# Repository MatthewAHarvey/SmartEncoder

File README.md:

# SmartEncoder
Arduino friendly, serially addressable, ATTINY85 based rotary encoders. Reduce the pin count from 3 * n where n is the number of encoders (pins A, B and button C) to 2 total. Serial in, Serial out. Use Hardware Serial, AltSoftSerial or Software Serial

Handling lots of encoders at the same time can be a challenge. For example, in our use case, we had 15 encoders attached to one Arduino Mega. After all the connections to other peripherals, we ran out of pins. The encoders had to be polled since there are not enough interrupts. Our solution is to offload the handling of the encoders to dedicated ATTINY85 chips. These then talk asynchronous serial at 125000 baud in a ring with the master arduino. The arduino now only needs 2 pins: 1 serial tx and 1 serial rx. At the moment this is limited to one of the hardware serial ports but tests show it's possible with software serial implementations.

In order for this to work, the ATTINY85s' clock frequencies must be set more accurately than straight from the factory. 

### Installation instructions:

1. First, the ATTINYs must be frequency calibrated. We do this by burning the arduino bootloader on to an ATTINY and uploading the FreqCal sketch. We use the [ATTINYCore](https://github.com/SpenceKonde/ATTinyCore) which must be installed in the Arduino IDE. We output a square wave from pin 6 and observe it using an oscilloscope. An attached rotary encoder is then used to adjust this signal until it is as close to 1 MHz as possible. Pressing the encoder button saves the current OSCCAL register value to the EEPROM. 

Arduino IDE settings for ATTINY85:

Schematic for the FreqCal rotary encoder programme:

2. Now upload the ATTINY85RotEncCode sketch to each of the ATTINYs.

3. The example SEHandlerTest programme can be uploaded to the master arduino mega.

### To Do:
1. Add individual encoder direction swap command that can be called any time after init().
2. Add global encoder direction swap at creation time that tells all the individual encoders to swap direction at init time.

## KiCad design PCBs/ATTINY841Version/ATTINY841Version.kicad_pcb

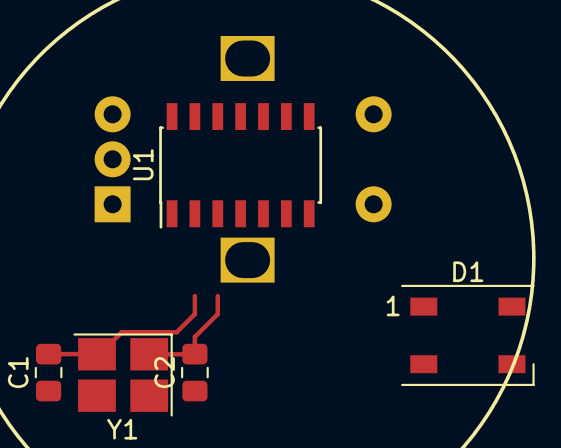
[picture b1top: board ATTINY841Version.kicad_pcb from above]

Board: 2 copper layers, 6 parts (1 on the bottom side), 3 nets.

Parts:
C1, C2: C; C_0805_2012Metric_Pad1.15x1.40mm_HandSolder
D1: WS2812B; LED_WS2812B_PLCC4_5.0x5.0mm_P3.2mm
SW1: Rotary_Encoder_Switch; RotaryEncoder_Alps_EC12E-Switch_Vertical_H20mm
U1: ATtiny841-SSU; SOIC-14_3.9x8.7mm_P1.27mm
Y1: Crystal; Crystal_SMD_3225-4Pin_3.2x2.5mm_HandSoldering

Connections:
/XTAL1: C1.2, U1.2, Y1.2
/XTAL2: C2.2, U1.3, Y1.1
GND: C1.1, C2.1, SW1.C, SW1.S2, U1.14

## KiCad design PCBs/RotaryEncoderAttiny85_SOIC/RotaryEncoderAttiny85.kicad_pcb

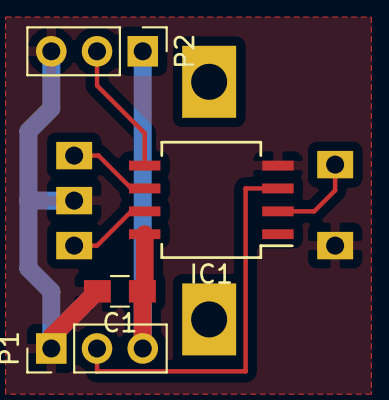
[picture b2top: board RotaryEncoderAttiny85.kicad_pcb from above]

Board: 2 copper layers, 5 parts (1 on the bottom side), 7 nets.

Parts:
C1: C; C_0805_HandSoldering
IC1: ATTINY85-P; SO-8_5.3x6.2mm_Pitch1.27mm
P1, P2: CONN_01X03; Pin_Header_Straight_1x03_Pitch2.54mm
SW1: Rotary_Encoder_Switch; RotEnc

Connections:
+5V: C1.1, IC1.8, P1.3, P2.1
GND: C1.2, IC1.4, P1.1, P2.3, SW1.2, SW1.5
unnamed: IC1.2, SW1.4
unnamed: IC1.3, P1.2
unnamed: IC1.5, P2.2
unnamed: IC1.6, SW1.3
unnamed: IC1.7, SW1.1

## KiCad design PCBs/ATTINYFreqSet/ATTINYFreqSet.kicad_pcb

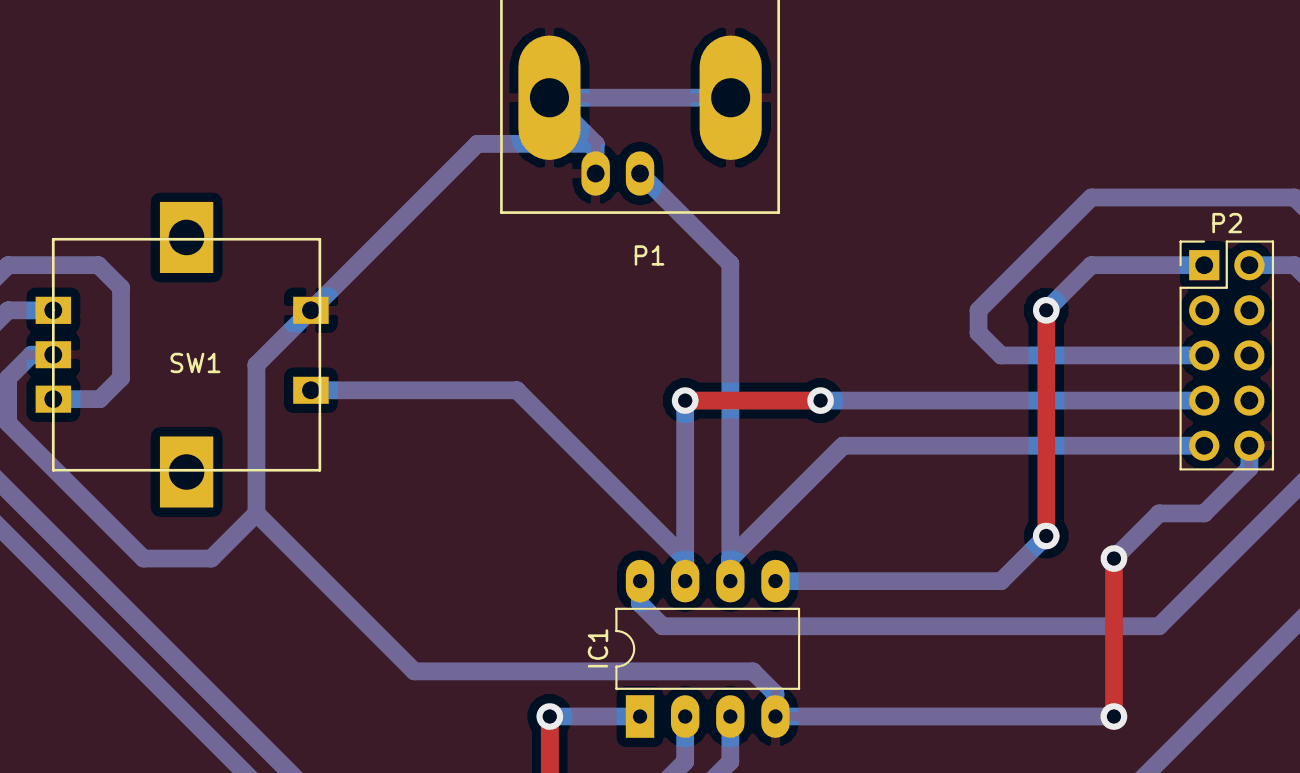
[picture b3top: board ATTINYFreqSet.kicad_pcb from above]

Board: 2 copper layers, 4 parts (0 on the bottom side), 8 nets.

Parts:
IC1: ATTINY85-P; DIP-8_W7.62mm_LongPads
P1: BNC; BNC_Socket_TYCO-AMP_LargePads
P2: CONN_02X05; Pin_Header_Straight_2x05_Pitch2.54mm
SW1: Rotary_Encoder_Switch; RotEnc

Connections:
+5V: IC1.8, P2.2
GND: IC1.4, P1.2, P2.10, SW1.2, SW1.5
unnamed: IC1.1, P2.5
unnamed: IC1.2, SW1.1
unnamed: IC1.3, SW1.3
unnamed: IC1.5, P2.1
unnamed: IC1.6, P1.1, P2.9
unnamed: IC1.7, P2.7, SW1.4

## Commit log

2018-04-25 Moved settings image file
2018-04-25 Changed filename
2018-04-25 Revert "Update README.md"
    This reverts commit 41cb5acd82bd45d6b810ba44660a57af6422a5ea.
2018-04-25 Updated readme and added a schematic
2018-04-25 Fixed errror
2018-04-25 changed png to PNG
2018-04-26 Tweaked defaults. Removed accidentally added junk code at bottom of sketch
2018-04-28 Added Rateless option to poll()
    Sometimes you don't want to have to check for turn rate1, 2 or 3 and only want to know which way the encoder was rotated. poll(true) or poll_rateless return all clockwise events as CW_RATE1 and antic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
2018-04-28 Rateless options added to Encoder class as well
2018-04-28 Added default bool to timedOut and removed pointless overloaded function
2018-04-28 Forgot to update some files
2018-12-13 Some fixes and added PCBs
    I haven't looked at this in a while but here are some PCBs and a few bug fixes to the code. The code is about to get an overhaul to make it more readable but is working as is.
    The PCBs are in use except for the SOIC version which I haven't tested yet.
2019-09-17 attiny841 work in progress
    Work in progress for different chip
2019-10-15 Added blank constructor and additional init function
